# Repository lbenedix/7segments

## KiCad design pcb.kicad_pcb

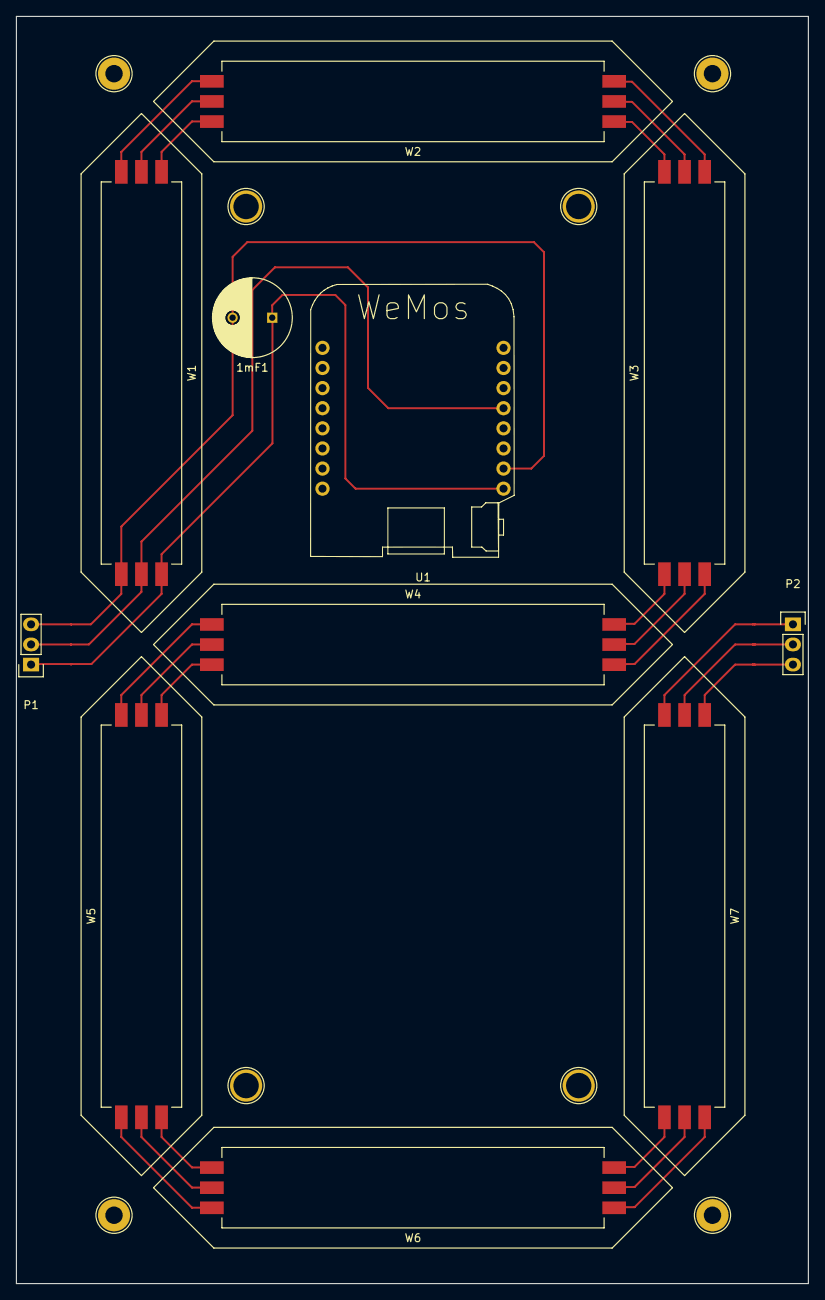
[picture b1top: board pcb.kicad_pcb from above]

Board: 2 copper layers, 100.0 x 160.0 mm, 11 parts (0 on the bottom side), 24 nets.

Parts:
1mF1: CP; C_Radial_D10_L16_P5
P1, P2: CONN_01X03; Pin_Header_Straight_1x03
U1: WeMos_mini; D1_mini_board
W1, W2, W3, W4, W5, W6, W7: WS2812Bx3; WS2812b

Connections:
unnamed: 1mF1.1, P1.1, U1.1, W1.3
unnamed: 1mF1.2, P1.3, U1.2, W1.1
unnamed: P1.2, U1.5, W1.2
unnamed: P2.1, W7.6
unnamed: P2.2, W7.5
unnamed: P2.3, W7.4
unnamed: W1.4, W2.3
unnamed: W1.5, W2.2
unnamed: W1.6, W2.1
unnamed: W2.4, W3.3
unnamed: W2.5, W3.2
unnamed: W2.6, W3.1
unnamed: W3.4, W4.3
unnamed: W3.5, W4.2
unnamed: W3.6, W4.1
unnamed: W4.4, W5.3
unnamed: W4.5, W5.2
unnamed: W4.6, W5.1
unnamed: W5.4, W6.3
unnamed: W5.5, W6.2
unnamed: W5.6, W6.1
unnamed: W6.4, W7.3
unnamed: W6.5, W7.2
unnamed: W6.6, W7.1

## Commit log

2019-08-21 Update LICENSE
